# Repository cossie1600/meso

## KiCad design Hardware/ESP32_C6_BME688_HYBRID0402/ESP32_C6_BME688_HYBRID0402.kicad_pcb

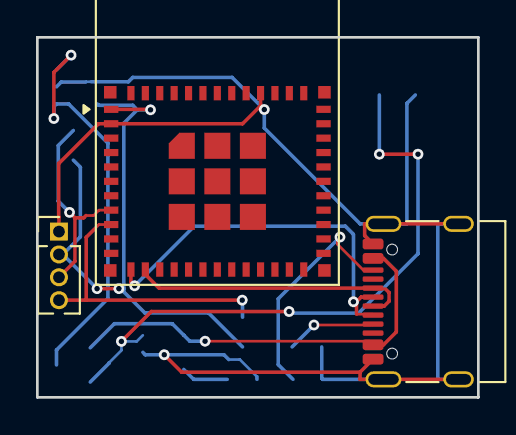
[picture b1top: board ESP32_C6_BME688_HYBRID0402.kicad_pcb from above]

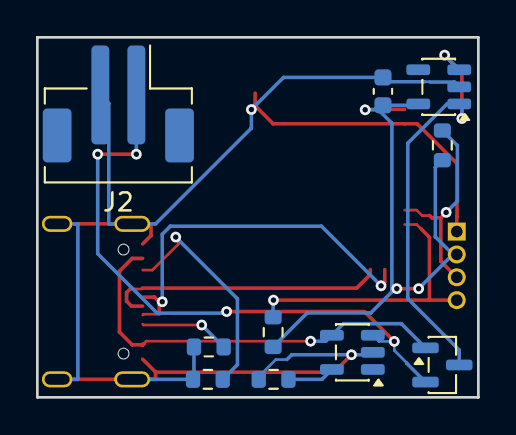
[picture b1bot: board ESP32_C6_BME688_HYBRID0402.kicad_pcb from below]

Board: 2 copper layers, 24.5 x 20.0 mm, 13 parts (10 on the bottom side), 12 nets.

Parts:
C1: 100nF; C_0603_1608Metric
D1: BAT54C; SOT-23
J1: USB_C; USB_C_Receptacle_Palconn_UTC16-G
J2: JST_PH_2PIN; JST_PH_B2B-PH-SM4-TB_1x02-1MP_P2.00mm_Vertical
J3: Daughterboard_Interface; PinHeader_1x04_P1.27mm_Vertical
R1, R2: 4.7k; R_0603_1608Metric
R3, R4: 5.1k; R_0603_1608Metric
R5: 10k; R_0603_1608Metric
U1: ESP32-C6-MINI-1
U3: MCP73831; SOT-23-5
U4: AP2112K-3.3; SOT-23-5

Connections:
+3V3: C1.1, J3.2, R1.1, R2.1, U1.1, U4.5
CC1: J1.A5, R3.1
CC2: J1.B5, R4.1
GND: C1.2, J1.A1, J1.A12, J1.B1, J1.B12, J1.SH, J2.2, J3.1, R3.2, R4.2, R5.2, U1.2, U1.39, U3.2, U4.2
I2C0_SCL: J3.4, R2.2, U1.9
I2C0_SDA: J3.3, R1.2, U1.8
PROG: R5.1, U3.5
USB_DM: J1.A7, J1.B7, U1.12
USB_DP: J1.A6, J1.B6, U1.13
VBAT: D1.2, J2.1, U3.3
VBUS_5V: D1.1, J1.A4, J1.A9, J1.B4, J1.B9, U3.4
VSYS: D1.3, U4.1, U4.3

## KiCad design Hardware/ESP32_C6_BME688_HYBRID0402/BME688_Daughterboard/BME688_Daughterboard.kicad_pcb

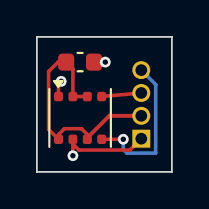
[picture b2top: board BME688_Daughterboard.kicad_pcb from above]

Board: 2 copper layers, 7.5 x 7.5 mm, 3 parts (1 on the bottom side), 4 nets.

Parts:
C2: 100nF; C_0603_1608Metric
J4: Carrier_Header; PinHeader_1x04_P1.27mm_Horizontal
U2: BME688; Bosch_LGA-8_3x3mm_P0.8mm_ClockwisePinNumbering

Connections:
+3V3: C2.1, J4.2, U2.2, U2.3, U2.6, U2.8
GND: C2.2, J4.1, U2.1, U2.7
I2C0_SCL: J4.4, U2.5
I2C0_SDA: J4.3, U2.4

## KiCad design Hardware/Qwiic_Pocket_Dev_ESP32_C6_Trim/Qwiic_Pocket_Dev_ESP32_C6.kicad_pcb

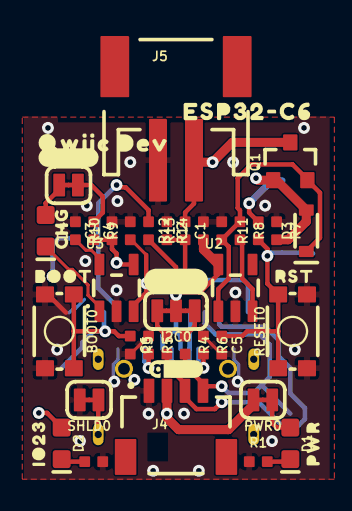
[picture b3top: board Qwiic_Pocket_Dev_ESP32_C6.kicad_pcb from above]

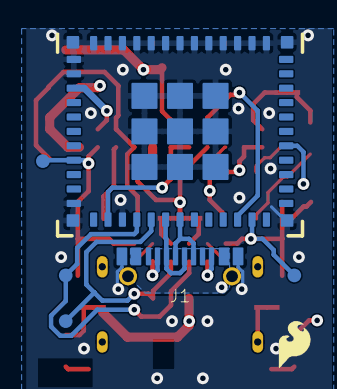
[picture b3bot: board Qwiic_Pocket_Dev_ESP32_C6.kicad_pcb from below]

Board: 4 copper layers, 52 parts (7 on the bottom side), 27 nets.

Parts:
BOOT0: MOMENTARY-SWITCH-SPST-SMD-4.6X2.8MM; TACTILE_SWITCH_SMD_4.6X2.8MM
C1, C2, C3, C4: 2.2uF; 0402-TIGHT
C5: 0.1uF; 0402-TIGHT
C6: DNP; 0402-TIGHT
CHG0: JUMPER-SMT_2_NC_TRACE_SILK; SMT-JUMPER_2_NC_TRACE_SILK
D1: LED-0603
D2: BLUE; LED-0603
D3: 1A/23V/620mV; SOD-323
D4: Yellow; LED-0603
I2C0: JUMPER-SMT_3_2-NC_TRACE_SILK; SMT-JUMPER_3_2-NC_TRACE_SILK
J1: USB Female Type C Connector; USB-C-16P_4LAYER-PADS
J4: QWIIC_RIGHT_ANGLE; JST04_1MM_RA
J5: JST-2-SMD
LOGO3: QWIIC_LOGO_3MM; QWIIC_3MM
PWR0: JUMPER-SMT_2_NC_TRACE_SILK; SMT-JUMPER_2_NC_TRACE_SILK
Q1: 20V/4.2A/52mΩ/1.4W; SOT23-3
R1, R9, R10: 4.7k; 0402-TIGHT
R2, R3, R4: 2.2k; 0402-TIGHT
R5, R6: 5.1k; 0402-TIGHT
R7, R8, R11, R12: 100k; 0402-TIGHT
R13, R14: 1M; 0402-TIGHT
RESET0: MOMENTARY-SWITCH-SPST-SMD-4.6X2.8MM; TACTILE_SWITCH_SMD_4.6X2.8MM
SHLD0: JUMPER-SMT_2_NC_TRACE_SILK; SMT-JUMPER_2_NC_TRACE_SILK
TP1, TP2, TP3, TP4: TEST-POINT3; PAD.03X.03
U1: ESP32-C6-MINI-1
U2: RT9080-33GJ5; SOT23-5
U3: MCP73831; SOT23-5
U$10: SFE_LOGO_FLAME_.1
U$12: ESP32#C633
U$23: #I�C#0
U$25: QWIIC_DEV0
U$28: IO230
U$30: PWR0
U$31: #CHG#0
U$32: CHG0
U$33: BOOT0
U$34: RST0

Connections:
3.3V: C2.1, I2C0.2, J4.2, PWR0.2, R11.2, R12.2, U1.3, U2.5
EN: C5.1, R11.1, RESET0.3, RESET0.4, TP4.1, U1.8
GND: BOOT0.1, BOOT0.2, C1.2, C2.2, C3.2, C4.2, C5.2, C6.2, J1.GND, J1.GND2, J4.1, J5.1, R1.1, R2.1, R5.1, R6.1, R7.1, R10.1, R14.1, RESET0.1, RESET0.2, SHLD0.2, U1.1, U1.2, U1.11, U1.14, U1.36, U1.37, U1.38, U1.39, U1.40, U1.41, U1.42, U1.43, U1.44, U1.45, U1.46, U1.47, U1.48, U1.49.1, U1.49.2, U1.49.3, U1.49.4, U1.49.5, U1.49.6, U1.49.7, U1.49.8, U1.49.9, U1.50, U1.51, U1.52, U1.53, U2.2, U3.2
IO1/V_BATT_2: R13.1, R14.2, U1.13
IO6/SDA: J4.3, R3.1, TP2.1, U1.15
IO7/SCL: J4.4, R4.2, TP1.1, U1.16
IO9/BOOT: BOOT0.3, BOOT0.4, C6.1, TP3.1, U1.23
IO12/USB_N: J1.A7, J1.B7, U1.17
IO13/USB_P: J1.A6, J1.B6, U1.18
IO23/STAT: D2.A, U1.29
unnamed: D1.C, R1.2
unnamed: D1.A, PWR0.1
unnamed: D2.C, R2.2
unnamed: I2C0.3, R3.2
unnamed: I2C0.1, R4.1
unnamed: R8.2, U2.3
unnamed: J1.B5, R5.2
unnamed: J1.A5, R6.2
unnamed: C1.1, D3.C, Q1.2, R8.1, U2.1
unnamed: D4.C, U3.1
unnamed: CHG0.1, D4.A
unnamed: CHG0.2, R9.1
unnamed: R10.2, U3.5
unnamed: R12.1, U1.22
SHLD: J1.SHLD1, J1.SHLD2, J1.SHLD3, J1.SHLD4, SHLD0.1
V_BATT: C4.1, J5.2, Q1.3, R13.2, U3.3
V_USB: C3.1, D3.A, J1.VBUS1, J1.VBUS2, Q1.1, R7.2, R9.2, U3.4
